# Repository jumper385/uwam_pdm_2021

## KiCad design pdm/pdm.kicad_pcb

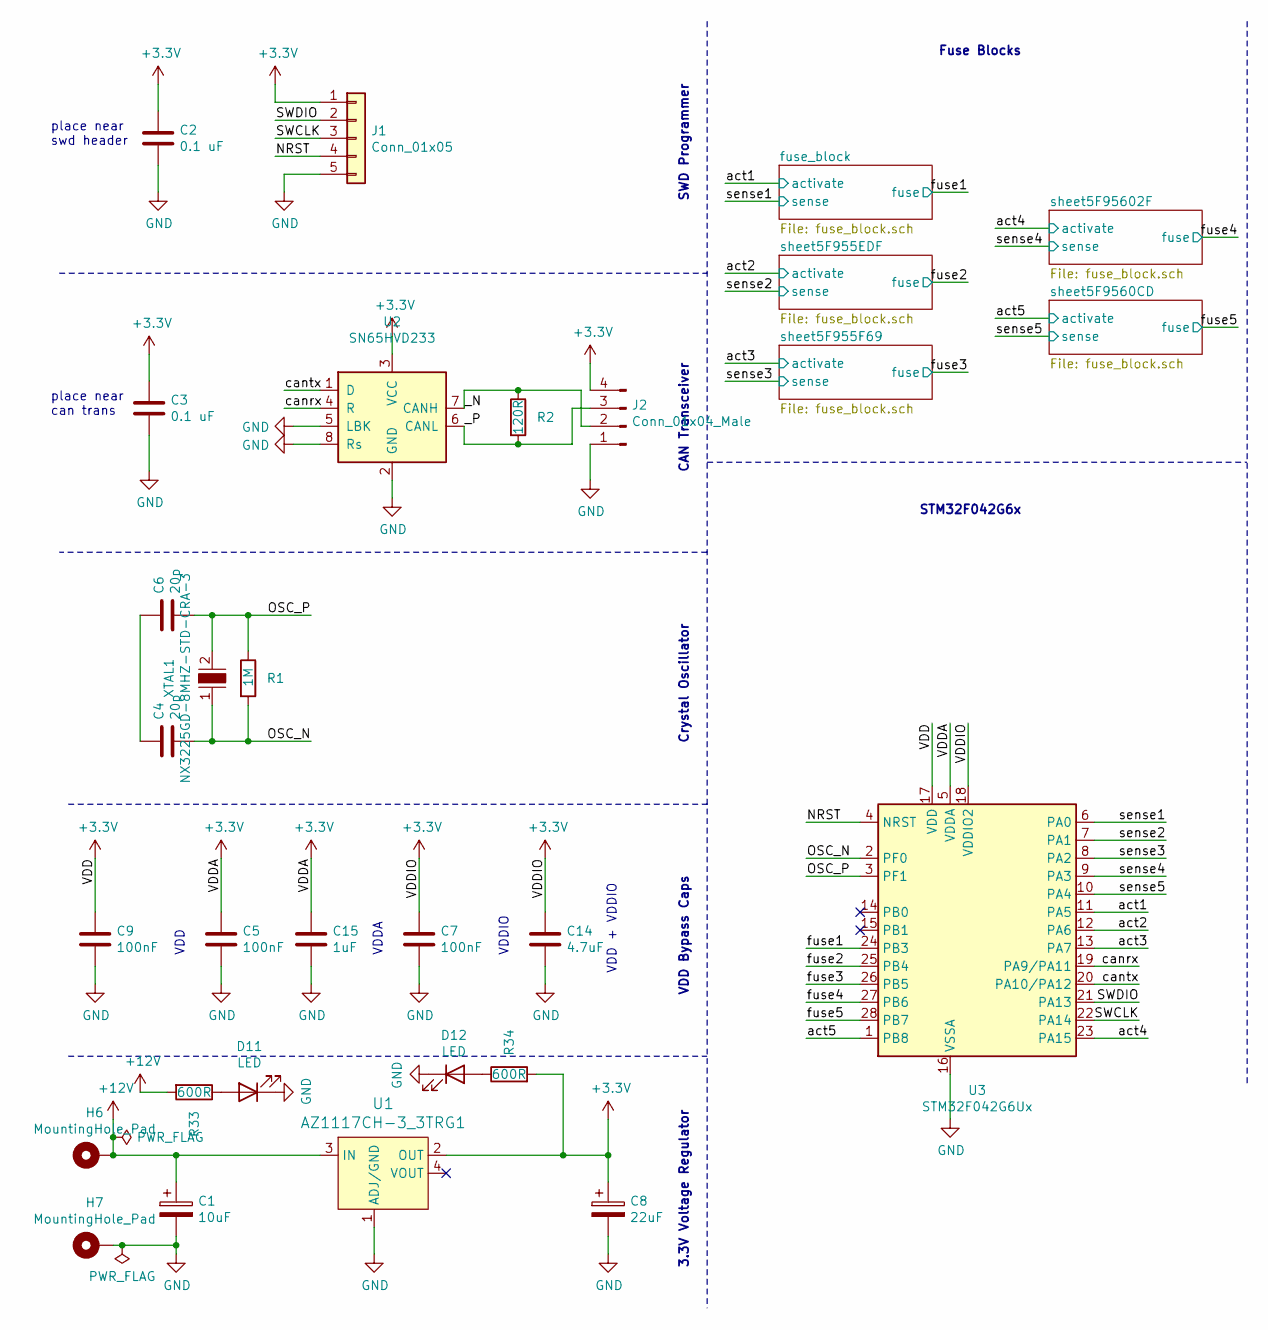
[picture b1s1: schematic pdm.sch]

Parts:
C1: 10uF; CP_Elec_4x5.4; Digi-Key_PN PCE3895CT-ND
C2, C3: 0.1 uF; C_0805_2012Metric_Pad1.15x1.40mm_HandSolder
C4, C6: 20p; C_0805_2012Metric_Pad1.15x1.40mm_HandSolder
C5, C7, C9: 100nF; C_0805_2012Metric_Pad1.15x1.40mm_HandSolder
C8: 22uF; CP_Elec_6.3x5.8; Digi-Key_PN PCE4964CT-ND
C14: 4.7uF; C_0805_2012Metric_Pad1.15x1.40mm_HandSolder
C15: 1uF; C_0805_2012Metric_Pad1.15x1.40mm_HandSolder
D11, D12: LED; LED_0805_2012Metric_Pad1.15x1.40mm_HandSolder
H6, H7: MountingHole_Pad; MountingHole_4mm_Pad_Via
J1: Conn_01x05; PinHeader_1x05_P2.00mm_Vertical
J2: Conn_01x04_Male; PinHeader_1x04_P2.00mm_Horizontal
R1: 1M; R_0805_2012Metric_Pad1.15x1.40mm_HandSolder
R2: 120R; R_0805_2012Metric_Pad1.15x1.40mm_HandSolder
R33, R34: 600R; R_0805_2012Metric_Pad1.15x1.40mm_HandSolder
U1: AZ1117CH-3_3TRG1; SOT-223; MPN AZ1117CH-3.3TRG1; Digi-Key_PN AZ1117CH-3.3TRG1DICT-ND
U2: SN65HVD233; SOIC-8_3.9x4.9mm_P1.27mm
U3: STM32F042G6Ux; QFN-28_4x4mm_P0.5mm
XTAL1: NX3225GD-8MHZ-STD-CRA-3; SMD-2_3.2x2.5mm; MPN NX3225GD-8MHZ-STD-CRA-3; Digi-Key_PN 644-1178-1-ND

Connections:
+3V3: C2.1, C3.1, C5.1, C7.1, C8.1, C9.1, C14.1, C15.1, J1.1, J2.4, R34.2, U1.2 (OUT), U2.3 (VCC), U3.5 (VDDA), U3.17 (VDD), U3.18 (VDDIO2); also elsewhere on the board
+12V: C1.1, H6.1, R33.2, U1.3 (IN); also elsewhere on the board
/NRST: J1.4, U3.4 (NRST)
/OSC_N: C4.2, R1.2, U3.2 (PF0), XTAL1.1
/OSC_P: C6.2, R1.1, U3.3 (PF1), XTAL1.2
/SWCLK: J1.3, U3.22 (PA14)
/SWDIO: J1.2, U3.21 (PA13)
/_N: J2.2, R2.1, U2.7 (CANH)
/_P: J2.3, R2.2, U2.6 (CANL)
/act1: U3.11 (PA5); also elsewhere on the board
/act2: U3.12 (PA6); also elsewhere on the board
/act3: U3.13 (PA7); also elsewhere on the board
/act4: U3.23 (PA15); also elsewhere on the board
/act5: U3.1 (PB8); also elsewhere on the board
/canrx: U2.4 (R), U3.19 (PA9/PA11)
/cantx: U2.1 (D), U3.20 (PA10/PA12)
/fuse1: U3.24 (PB3); also elsewhere on the board
/fuse2: U3.25 (PB4); also elsewhere on the board
/fuse3: U3.26 (PB5); also elsewhere on the board
/fuse4: U3.27 (PB6); also elsewhere on the board
/fuse5: U3.28 (PB7); also elsewhere on the board
/sense1: U3.6 (PA0); also elsewhere on the board
/sense2: U3.7 (PA1); also elsewhere on the board
/sense3: U3.8 (PA2); also elsewhere on the board
/sense4: U3.9 (PA3); also elsewhere on the board
/sense5: U3.10 (PA4); also elsewhere on the board
GND: C1.2, C2.2, C3.2, C5.2, C7.2, C8.2, C9.2, C14.2, C15.2, D11.1 (K), D12.1 (K), H7.1, J1.5, J2.1, U1.1 (ADJ/GND), U2.2 (GND), U2.5 (LBK), U2.8 (Rs), U3.16 (VSSA); also elsewhere on the board
unnamed: C4.1, C6.1
unnamed: D11.2 (A), R33.1
unnamed: D12.2 (A), R34.1

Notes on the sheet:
place near swd header
place near can trans
SWD Programmer
CAN Transceiver
Crystal Oscillator
VDD Bypass Caps
3.3V Voltage Regulator
VDD + VDDIO
STM32F042G6x
Fuse Blocks
VDD
VDDA
VDDIO

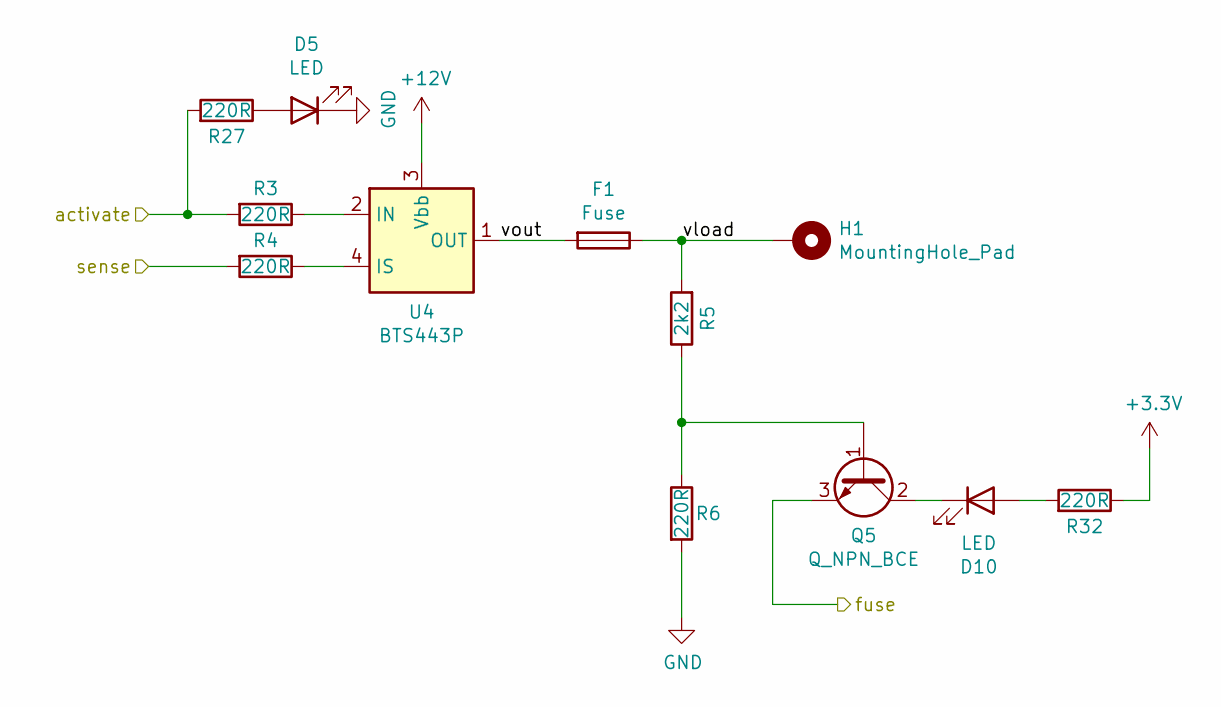
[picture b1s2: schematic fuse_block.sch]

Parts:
D4, D9: LED; LED_0805_2012Metric_Pad1.15x1.40mm_HandSolder
F5: Fuse; Fuse_Blade_ATO_directSolder
H5: MountingHole_Pad; MountingHole_4mm_Pad_Via
Q3: Q_NPN_BCE; SOT-23_Handsoldering
R19, R20, R22, R26, R31: 220R; R_0805_2012Metric_Pad1.15x1.40mm_HandSolder
R21: 2k2; R_0805_2012Metric_Pad1.15x1.40mm_HandSolder
U12: BTS443P; TO-252-4

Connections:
+3V3: R31.1; also elsewhere on the board
+12V: U12.3 (Vbb); also elsewhere on the board
/act1: R19.2, R26.2; also elsewhere on the board
/fuse3: Q3.3 (E); also elsewhere on the board
/fuse_block/vload: F5.1, H5.1, R21.2
/fuse_block/vout: F5.2, U12.1 (OUT), U12.5 (OUT)
/sense1: R20.2; also elsewhere on the board
GND: D4.1 (K), R22.2; also elsewhere on the board
unnamed: D4.2 (A), R26.1
unnamed: D9.2 (A), R31.2
unnamed: R19.1, U12.2 (IN)
unnamed: R20.1, U12.4 (IS)

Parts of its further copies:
D1, D2, D3, D5, D6, D7, D8, D10: LED; LED_0805_2012Metric_Pad1.15x1.40mm_HandSolder
F1, F2, F3, F4: Fuse; Fuse_Blade_ATO_directSolder
H1, H2, H3, H4: MountingHole_Pad; MountingHole_4mm_Pad_Via
Q1, Q2, Q4, Q5: Q_NPN_BCE; SOT-23_Handsoldering
R3, R4, R6, R7, R8, R10, R11, R12, R14, R15, R16, R18, R23, R24, R25, R27, R28, R29, R30, R32: 220R; R_0805_2012Metric_Pad1.15x1.40mm_HandSolder
R5, R9, R13, R17: 2k2; R_0805_2012Metric_Pad1.15x1.40mm_HandSolder
U4, U6, U8, U10: BTS443P; TO-252-4

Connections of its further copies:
+3V3: R28.1, R29.1, R30.1, R32.1; also elsewhere on the board
+12V: U4.3 (Vbb), U6.3 (Vbb), U8.3 (Vbb), U10.3 (Vbb); also elsewhere on the board
/act2: R3.2, R27.2; also elsewhere on the board
/act3: R7.2, R25.2; also elsewhere on the board
/act4: R11.2, R24.2; also elsewhere on the board
/act5: R15.2, R23.2; also elsewhere on the board
/fuse1: Q4.3 (E); also elsewhere on the board
/fuse2: Q5.3 (E); also elsewhere on the board
/fuse4: Q2.3 (E); also elsewhere on the board
/fuse5: Q1.3 (E); also elsewhere on the board
/sense2: R4.2; also elsewhere on the board
/sense3: R8.2; also elsewhere on the board
/sense4: R12.2; also elsewhere on the board
/sense5: R16.2; also elsewhere on the board
/sheet5F955EDF/vload: F1.1, H1.1, R5.2
/sheet5F955EDF/vout: F1.2, U4.1 (OUT), U4.5 (OUT)
/sheet5F955F69/vload: F2.1, H2.1, R9.2
/sheet5F955F69/vout: F2.2, U6.1 (OUT), U6.5 (OUT)
/sheet5F9560CD/vload: F4.1, H4.1, R17.2
/sheet5F9560CD/vout: F4.2, U10.1 (OUT), U10.5 (OUT)
/sheet5F95602F/vload: F3.1, H3.1, R13.2
/sheet5F95602F/vout: F3.2, U8.1 (OUT), U8.5 (OUT)
GND: D1.1 (K), D2.1 (K), D3.1 (K), D5.1 (K), R6.2, R10.2, R14.2, R18.2; also elsewhere on the board
unnamed: D1.2 (A), R23.1
unnamed: D2.2 (A), R24.1
unnamed: D3.2 (A), R25.1
unnamed: D5.2 (A), R27.1
unnamed: D6.1 (K), Q1.2 (C)
unnamed: D6.2 (A), R28.2
unnamed: D7.1 (K), Q2.2 (C)
unnamed: D7.2 (A), R29.2
unnamed: D8.2 (A), R30.2
unnamed: D10.1 (K), Q5.2 (C)
unnamed: D10.2 (A), R32.2
unnamed: Q1.1 (B), R17.1, R18.1
unnamed: Q2.1 (B), R13.1, R14.1
unnamed: Q5.1 (B), R5.1, R6.1
unnamed: R3.1, U4.2 (IN)
unnamed: R4.1, U4.4 (IS)
unnamed: R7.1, U6.2 (IN)
unnamed: R8.1, U6.4 (IS)
unnamed: R11.1, U8.2 (IN)
unnamed: R12.1, U8.4 (IS)
unnamed: R15.1, U10.2 (IN)
unnamed: R16.1, U10.4 (IS)

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
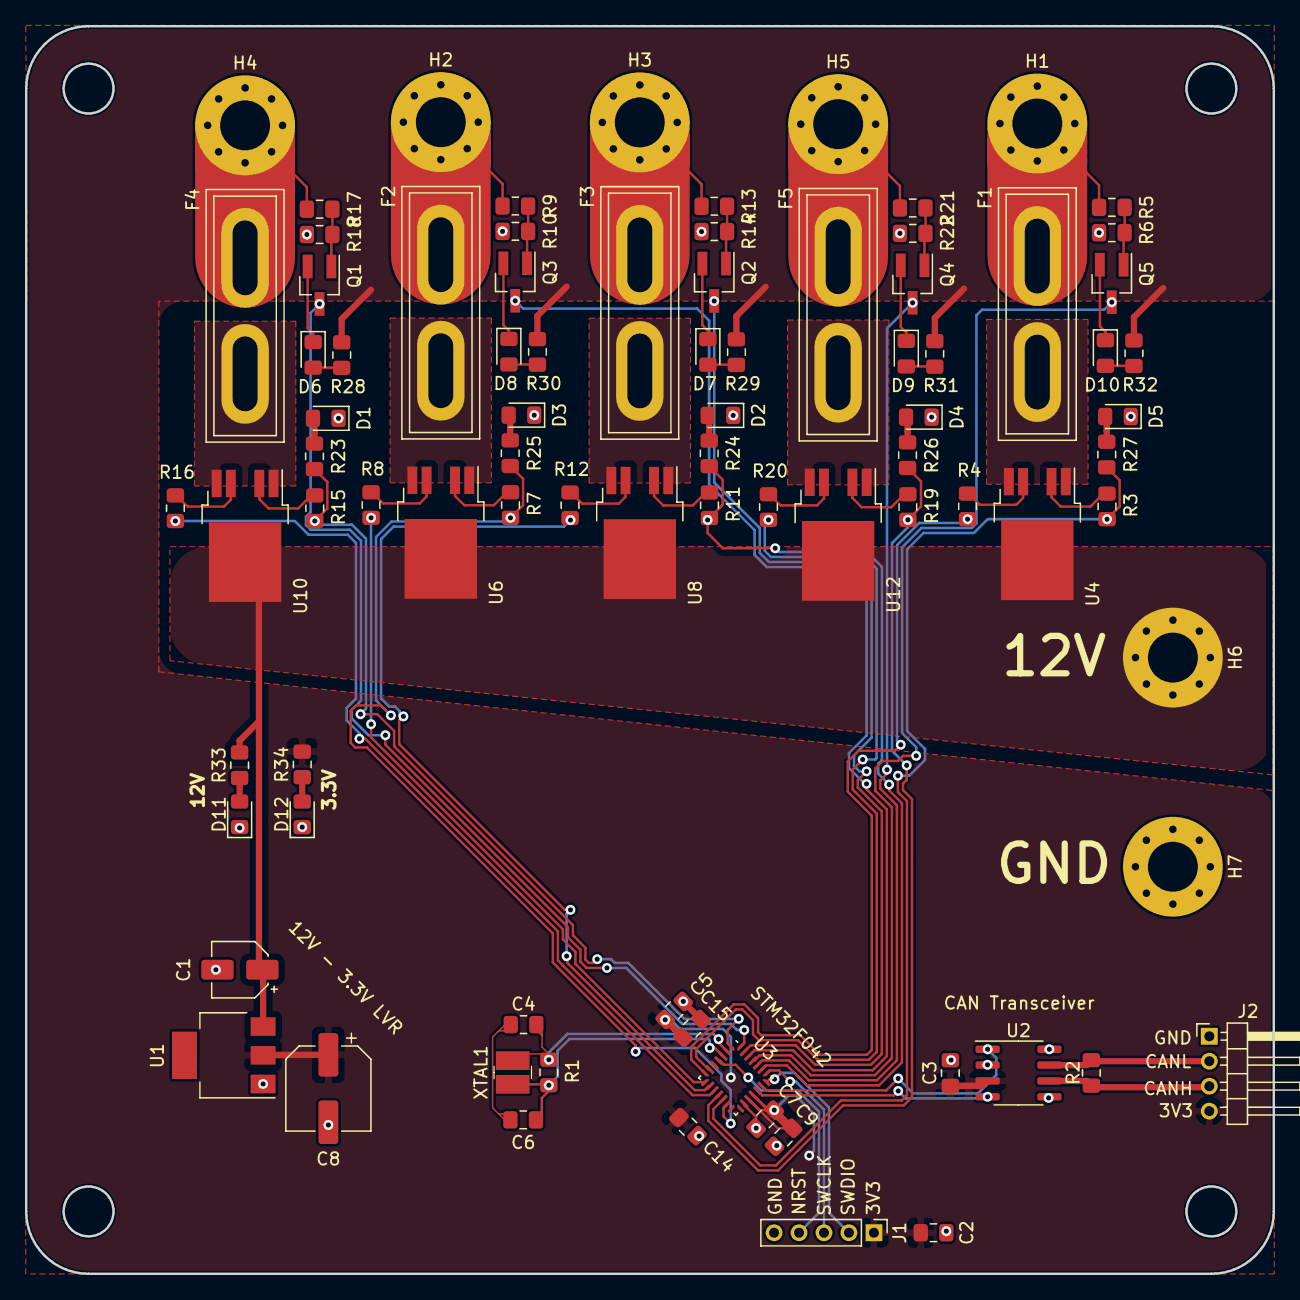
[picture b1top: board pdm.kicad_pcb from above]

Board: 2 copper layers, 100.0 x 100.0 mm, 85 parts (0 on the bottom side), 70 nets.

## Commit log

2020-10-25 uwam_pdm2021
2020-10-26 small changes
2020-10-26 layout duplication
2020-10-26 FUCK MANUAL ROUTING
2020-10-27 better routing
2020-10-29 replaced with stm32f042
2020-10-29 neatened up traces
2020-10-29 more neatening
